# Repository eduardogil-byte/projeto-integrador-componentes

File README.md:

# 🔍 Sistema de Inspeção Automatizada de PCBs

Sistema de visão computacional desenvolvido para auxiliar na **inspeção de lotes de placas de circuito impresso (PCBs)**.

O projeto surgiu a partir de uma **demanda real apresentada por uma instituição da área de pesquisa**, que precisava verificar placas eletrônicas de forma mais rápida e padronizada.

A aplicação utiliza os arquivos de fabricação da placa juntamente com fotografias da PCB montada para localizar e verificar seus componentes.

> 🚧 Projeto em fase final de desenvolvimento e validação.

---

## 📌 Sobre o projeto

A inspeção manual de placas eletrônicas pode exigir a conferência de dezenas ou centenas de componentes em cada PCB.

Quando esse processo precisa ser repetido em vários exemplares de um mesmo lote, a inspeção pode se tornar demorada e sujeita a inconsistências.

O objetivo deste projeto é utilizar **visão computacional** para auxiliar esse processo.

O sistema recebe informações da fabricação da placa e uma imagem da PCB montada, realiza o alinhamento entre elas e verifica individualmente os componentes esperados.

---

## 🎯 Objetivo

O sistema foi desenvolvido para auxiliar na identificação de problemas como:

* componentes ausentes;
* componentes cuja presença não pôde ser confirmada;
* diferenças entre a placa montada e os dados esperados;
* problemas de alinhamento ou qualidade da imagem que impeçam uma inspeção confiável.

O objetivo não é apenas indicar um resultado, mas também facilitar a análise do operador durante a inspeção de um lote.

---

## 🧠 Como funciona

De forma simplificada, o processo de inspeção segue este fluxo:

```text
Arquivos da placa
        +
Foto da PCB montada
        ↓
Identificação da placa
        ↓
Alinhamento por homografia
        ↓
Localização dos componentes
        ↓
Recorte das regiões de interesse
        ↓
Análise por visão computacional
        ↓
Classificação dos componentes
        ↓
Resultado da inspeção
```

---

## 📐 Alinhamento da placa

Uma das etapas mais importantes do sistema é alinhar corretamente a fotografia da placa real com a referência utilizada pelo software.

Para isso, o sistema utiliza **homografia**, permitindo relacionar as coordenadas dos componentes presentes nos arquivos de fabricação com suas posições na fotografia.

Esse processo permite que o software saiba onde cada componente deveria estar mesmo quando a imagem apresenta diferenças de:

* posição;
* escala;
* perspectiva;
* rotação.

Caso o alinhamento não possua qualidade suficiente, o sistema evita realizar classificações que poderiam produzir resultados incorretos.

---

## 🔎 Inspeção dos componentes

Após o alinhamento, cada região correspondente a um componente é localizada e recortada.

Essas imagens são analisadas individualmente para determinar se o componente está presente.

Os resultados podem ser classificados em estados como:

```text
✅ Presente
⚠️ Incerto
❌ Ausente
```

Resultados considerados incertos podem ser posteriormente avaliados pelo operador.

---

## 🧩 Dados da placa

O sistema utiliza informações provenientes dos arquivos de fabricação da PCB para saber quais componentes devem estar presentes e onde eles estão posicionados.

Entre as informações utilizadas estão dados como:

* referência do componente;
* coordenadas X e Y;
* encapsulamento;
* posição esperada na placa.

Esses dados são combinados com a análise da imagem da placa montada.

---

## 🛠️ Tecnologias utilizadas

O projeto utiliza diferentes ferramentas de visão computacional e desenvolvimento de software, incluindo:

* **Python**
* **OpenCV**
* **YOLO**
* **MobileNet**
* **Processamento de imagens**
* **Homografia**
* **Gerber**
* **Dados de posicionamento de componentes**
* **HTML**
* **CSS**
* **JavaScript**

---

## 🤖 Visão computacional

O sistema combina diferentes técnicas para realizar a inspeção.

### OpenCV

Utilizado em etapas de processamento e análise das imagens, incluindo transformações, recortes e alinhamento.

### Homografia

Responsável por relacionar a imagem capturada da placa com o sistema de coordenadas utilizado pelos arquivos da PCB.

### MobileNet

Utilizada na análise das regiões dos componentes para auxiliar na classificação da presença dos componentes.

### YOLO

Utilizado como parte do processo de detecção e alinhamento visual da placa.

---

## 🖥️ Interface

O software também possui uma interface para facilitar o processo de inspeção.

A interface permite acompanhar os resultados obtidos pelo sistema e identificar rapidamente componentes que precisam de atenção.

A proposta é manter o operador dentro do processo, permitindo que casos inconclusivos possam ser avaliados manualmente.

---

## 🏭 Aplicação prática

O projeto foi desenvolvido pensando em um cenário real de inspeção de **lotes de placas eletrônicas**.

Em vez de verificar manualmente cada posição da placa, o operador pode utilizar o software como apoio para identificar rapidamente regiões que apresentam possíveis problemas.

Isso permite concentrar a inspeção humana nos componentes que realmente precisam de análise.

---

## 📊 Resultados da inspeção

Durante uma inspeção, o sistema analisa individualmente os componentes esperados na placa e gera um resultado para cada posição.

Esses resultados podem então ser utilizados para visualizar:

* componentes confirmados;
* componentes que precisam de revisão;
* possíveis ausências;
* problemas relacionados à captura da imagem ou alinhamento.

---

## 🚧 Status do projeto

O software encontra-se em **fase final de desenvolvimento e validação**.

Esta versão representa a primeira implementação do sistema de inspeção e serviu como base para novas melhorias e experimentos realizados durante a evolução do projeto.

---

## 🎓 Contexto

O projeto foi desenvolvido como **Projeto Integrador**, partindo de uma necessidade apresentada por uma instituição atuante na área de pesquisa.

A proposta permitiu aplicar conhecimentos de desenvolvimento de software e visão computacional em um problema real relacionado à inspeção de placas eletrônicas.

---

## 🧠 Conceitos aplicados

Durante o desenvolvimento foram aplicados conceitos como:

* visão computacional;
* processamento de imagens;
* homografia;
* detecção de objetos;
* classificação de imagens;
* transformação de coordenadas;
* processamento de arquivos de fabricação de PCBs;
* integração entre frontend e processamento de imagens;
* validação de resultados;
* desenvolvimento orientado a uma necessidade real.

---

## 👨‍💻 Autores

**Eduardo Machado Gil**
GitHub: [@eduardogil-byte](https://github.com/eduardogil-byte)

**Luiz Gustavo da Silva Campos**
GitHub: [@luizcamposss](https://github.com/luizcamposss)

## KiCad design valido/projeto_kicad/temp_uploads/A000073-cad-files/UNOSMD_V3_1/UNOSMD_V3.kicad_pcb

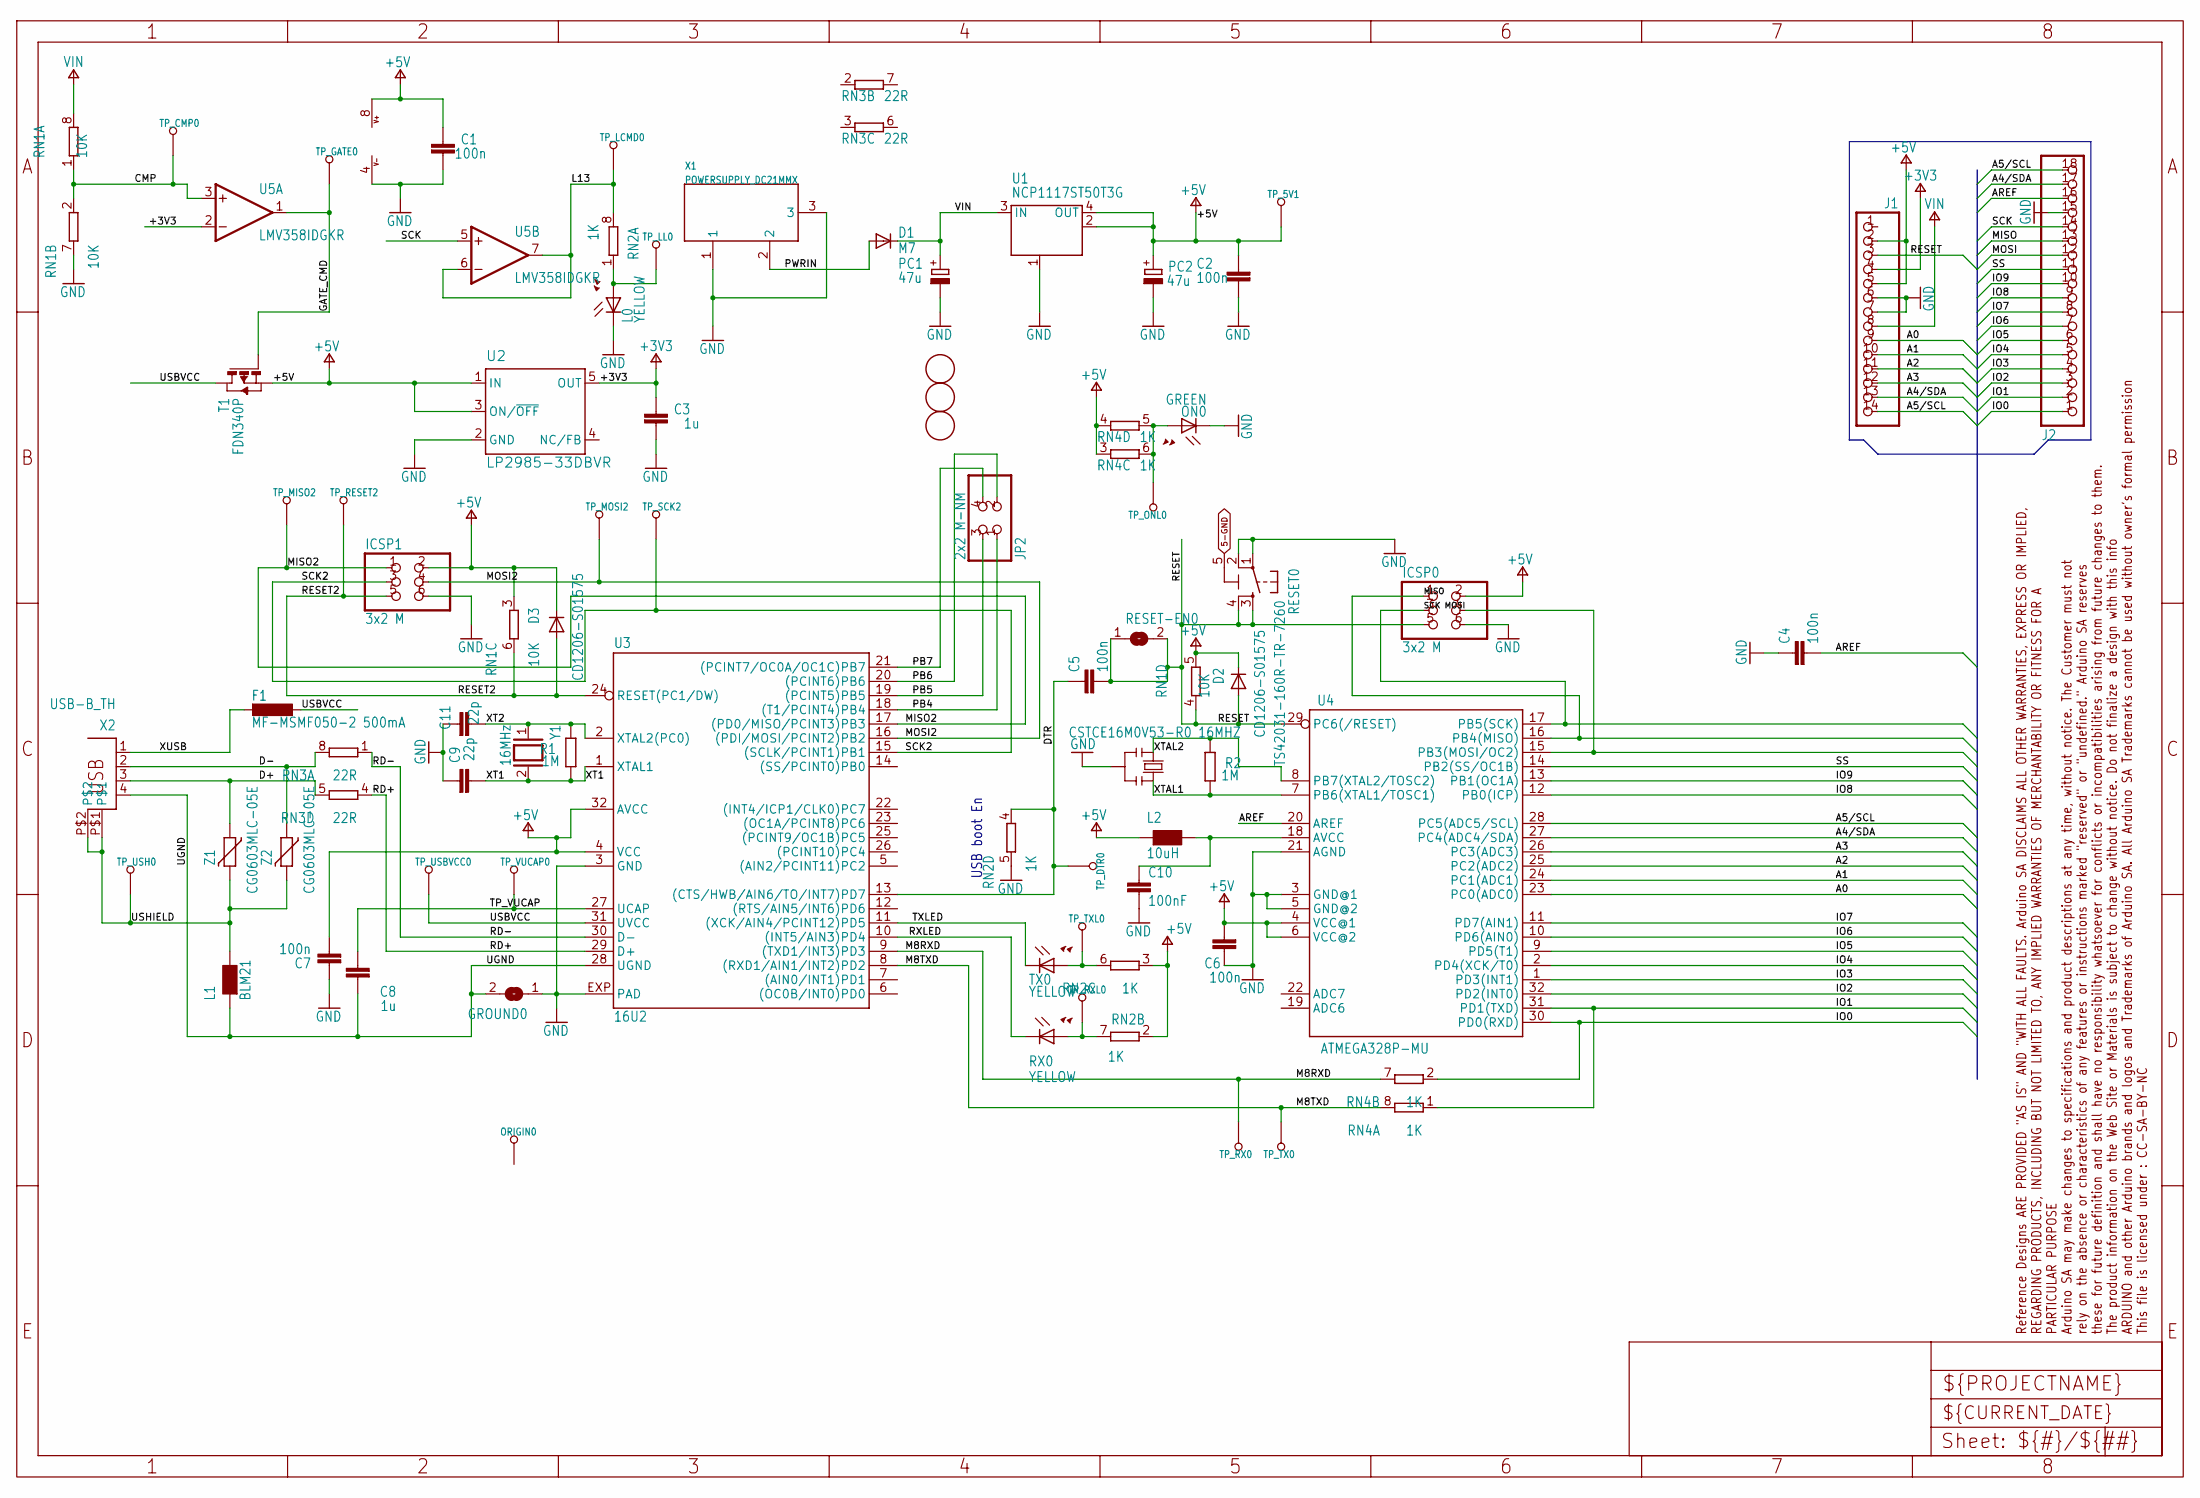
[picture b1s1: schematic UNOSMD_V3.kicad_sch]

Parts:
C1, C2, C4, C5, C6, C7: 100n; C0603-ROUND
C3, C8: 1u; C0603-ROUND
C9, C11: 22p; C0603-ROUND
C10: 100nF; C0603-ROUND
D1: M7; SMB
D2, D3: CD1206-S01575; MINIMELF
F1: MF-MSMF050-2 500mA; L1812
FD1, FD2, FD3: DNP; FD-1-1.5
FRAME1: DNP; FRAME
GROUND0: SJ
ICSP0, ICSP1: 3x2 M; 2X03
J1: -; 1X14-CUSTOM
J2: -; 1X18-CUSTOM
JP2: 2x2 M-NM; 2X02
L0: YELLOW; CHIP-LED0805
L1: BLM21; 0805
L2: 10uH; 0805
ON0: GREEN; CHIP-LED0805
ORIGIN0: TP_SP; TP-SP
PC1, PC2: 47u; PANASONIC_D
R1, R2: 1M; R0603-ROUND
RESET0: TS42031-160R-TR-7260; TS42
RESET-EN0: SJ
RN1: 10K; CAY16
RN2, RN4: 1K; CAY16
RN3: 22R; CAY16
RX0: YELLOW; CHIP-LED0805
T1: FDN340P; SOT-23
TP_5V1: TP_SP; TP-SP
TP_CMP0: TP_SP; TP-SP
TP_DTR0: TP_SP; TP-SP
TP_GATE0: TP_SP; TP-SP
TP_LCMD0: TP_SP; TP-SP
TP_LL0: TP_SP; TP-SP
TP_MISO2: TP_SP; TP-SP
TP_MOSI2: TP_SP; TP-SP
TP_ONL0: TP_SP; TP-SP
TP_RESET2: TP_SP; TP-SP
TP_RX0: TP_SP; TP-SP
TP_RXL0: TP_SP; TP-SP
TP_SCK2: TP_SP; TP-SP
TP_TX0: TP_SP; TP-SP
TP_TXL0: TP_SP; TP-SP
TP_USBVCC0: TP_SP; TP-SP
TP_USH0: TP_SP; TP-SP
TP_VUCAP0: TP_SP; TP-SP
TX0: YELLOW; CHIP-LED0805
U1: NCP1117ST50T3G; SOT223
U2: LP2985-33DBVR; SOT23-DBV
U3: 16U2; ATMEL_QFN32
U4: ATMEGA328P-MU; MLF32
U5: LMV358IDGKR; MSOP08
X1: POWERSUPPLY_DC21MMX; POWERSUPPLY_DC-21MM
X2: USB-B_TH; PN61729
Y1: 16MHz; QS
Y2: CSTCE16M0V53-R0 16MHZ; RESONATOR
Z1, Z2: CG0603MLC-05E; CT_CN0603

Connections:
5-GND: RESET0.5 (5-GND)
+3V3: C3.2, J1.4, U2.5 (OUT), U5.2 (-IN)
+5V: C1.2, C2.2, C6.2, C7.1, D2.C, D3.C, ICSP0.2, ICSP1.2, J1.2, J1.5, L2.1, PC2.+, RN1.3 (1), RN1.5 (2), RN2.2 (1), RN2.3 (1), RN4.3 (1), RN4.4 (1), T1.2 (S), TP_5V1.X, U1.2 (OUT@1), U1.4 (OUT), U2.1 (IN), U2.3 (ON/~OFF), U3.4 (VCC), U3.32 (AVCC), U4.4 (VCC@1), U4.6 (VCC@2), U5.8 (V+)
A0: J1.9, U4.23 (PC0(ADC0))
A1: J1.10, U4.24 (PC1(ADC1))
A2: J1.11, U4.25 (PC2(ADC2))
A3: J1.12, U4.26 (PC3(ADC3))
A4/SDA: J1.13, J2.17, U4.27 (PC4(ADC4/SDA))
A5/SCL: J1.14, J2.18, U4.28 (PC5(ADC5/SCL))
AREF: C4.2, J2.16, U4.20 (AREF)
CMP: RN1.1, RN1.2 (1), TP_CMP0.X, U5.3 (+IN)
D+: RN3.5 (2), X2.3, Z1.1
D-: RN3.8 (2), X2.2, Z2.1
DTR: C5.1, RN2.4 (1), TP_DTR0.X, U3.13 ((CTS/HWB/AIN6/TO/INT7)PD7)
GATE_CMD: T1.3 (G), TP_GATE0.X, U5.1 (OUT)
GND: C1.1, C2.1, C3.1, C4.1, C6.1, C7.2, C9.2, C10.2, C11.2, GROUND0.1, ICSP0.6, ICSP1.6, J1.6, J1.7, J2.15, L0.C, ON0.C, PC1.-, PC2.-, RESET0.1, RESET0.2, RN1.7 (2), RN2.5 (2), U1.1 (GND/ADJ), U2.2 (GND), U3.3 (GND), U3.EXP (PAD), U4.3 (GND@1), U4.5 (GND@2), U4.21 (AGND), U5.4 (V-), X1.1, X1.3, Y2.2
IO0: J2.1, RN4.2 (1), U4.30 (PD0(RXD))
IO1: J2.2, RN4.1, U4.31 (PD1(TXD))
IO2: J2.3, U4.32 (PD2(INT0))
IO3: J2.4, U4.1 (PD3(INT1))
IO4: J2.5, U4.2 (PD4(XCK/T0))
IO5: J2.6, U4.9 (PD5(T1))
IO6: J2.7, U4.10 (PD6(AIN0))
IO7: J2.8, U4.11 (PD7(AIN1))
IO8: J2.9, U4.12 (PB0(ICP))
IO9: J2.10, U4.13 (PB1(OC1A))
L13: RN2.8 (2), TP_LCMD0.X, U5.6 (-IN), U5.7 (OUT)
M8RXD: RN4.7 (2), TP_RX0.X, U3.9 ((TXD1/INT3)PD3)
M8TXD: RN4.8 (2), TP_TX0.X, U3.8 ((RXD1/AIN1/INT2)PD2)
MISO: ICSP0.1, J2.13, U4.16 (PB4(MISO))
MISO2: ICSP1.1, TP_MISO2.X, U3.17 ((PD0/MISO/PCINT3)PB3)
MOSI: ICSP0.4, J2.12, U4.15 (PB3(MOSI/OC2))
MOSI2: ICSP1.4, TP_MOSI2.X, U3.16 ((PDI/MOSI/PCINT2)PB2)
unnamed: L0.A, RN2.1, TP_LL0.X
unnamed: ON0.A, RN4.5 (2), RN4.6 (2), TP_ONL0.X
unnamed: C10.1, L2.2, U4.18 (AVCC)
unnamed: RN2.7 (2), RX0.A, TP_RXL0.X
unnamed: RN2.6 (2), TP_TXL0.X, TX0.A
PB4: JP2.1, U3.18 ((T1/PCINT4)PB4)
PB5: JP2.3, U3.19 ((PCINT5)PB5)
PB6: JP2.2, U3.20 ((PCINT6)PB6)
PB7: JP2.4, U3.21 ((PCINT7/OC0A/OC1C)PB7)
PWRIN: D1.A, X1.2
RD+: RN3.4 (1), U3.29 (D+)
RD-: RN3.1, U3.30 (D-)
RESET: C5.2, D2.A, ICSP0.5, J1.3, RESET0.3, RESET0.4, RESET-EN0.1, RESET-EN0.2, RN1.4 (1), U4.29 (PC6(/RESET))
RESET2: D3.A, ICSP1.5, RN1.6 (2), TP_RESET2.X, U3.24 (RESET(PC1/DW))
RXLED: RX0.C, U3.10 ((INT5/AIN3)PD4)
SCK: ICSP0.3, J2.14, U4.17 (PB5(SCK)), U5.5 (+IN)
SCK2: ICSP1.3, TP_SCK2.X, U3.15 ((SCLK/PCINT1)PB1)
SS: J2.11, U4.14 (PB2(SS/OC1B))
TP_VUCAP: C8.1, TP_VUCAP0.X, U3.27 (UCAP)
TXLED: TX0.C, U3.11 ((XCK/AIN4/PCINT12)PD5)
UGND: C8.2, GROUND0.2, L1.1, U3.28 (UGND), X2.4
USBVCC: F1.1, T1.1 (D), TP_USBVCC0.X, U3.31 (UVCC)
USHIELD: L1.2, TP_USH0.X, X2.P$1, X2.P$2, Z1.2, Z2.2
VIN: D1.C, J1.8, PC1.+, RN1.8 (2), U1.3 (IN)
XT1: C9.1, R1.1, U3.1 (XTAL1), Y1.2
XT2: C11.1, R1.2, U3.2 (XTAL2(PC0)), Y1.1
XTAL1: R2.1, U4.7 (PB6(XTAL1/TOSC1)), Y2.3
XTAL2: R2.2, U4.8 (PB7(XTAL2/TOSC2)), Y2.1
XUSB: F1.2, X2.1

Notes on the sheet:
USB boot En

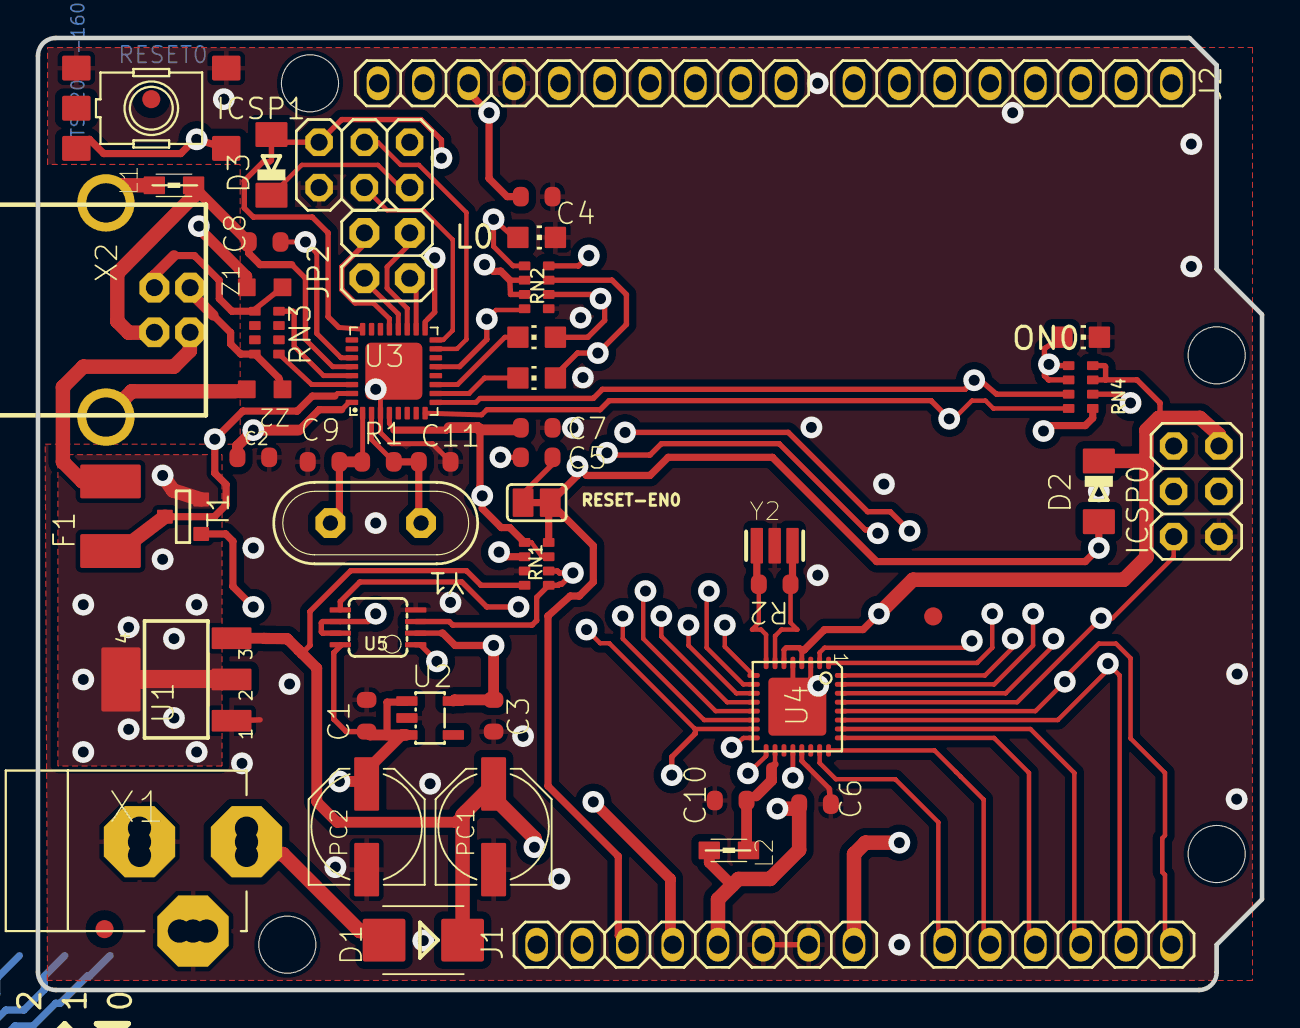
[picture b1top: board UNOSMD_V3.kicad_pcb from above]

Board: 2 copper layers, 68.6 x 53.3 mm, 76 parts (1 on the bottom side), 61 nets.

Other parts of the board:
UNK_HOLE_0: dummyfp0
UNK_HOLE_1: dummyfp1
UNK_HOLE_2: dummyfp2
UNK_HOLE_3: dummyfp3

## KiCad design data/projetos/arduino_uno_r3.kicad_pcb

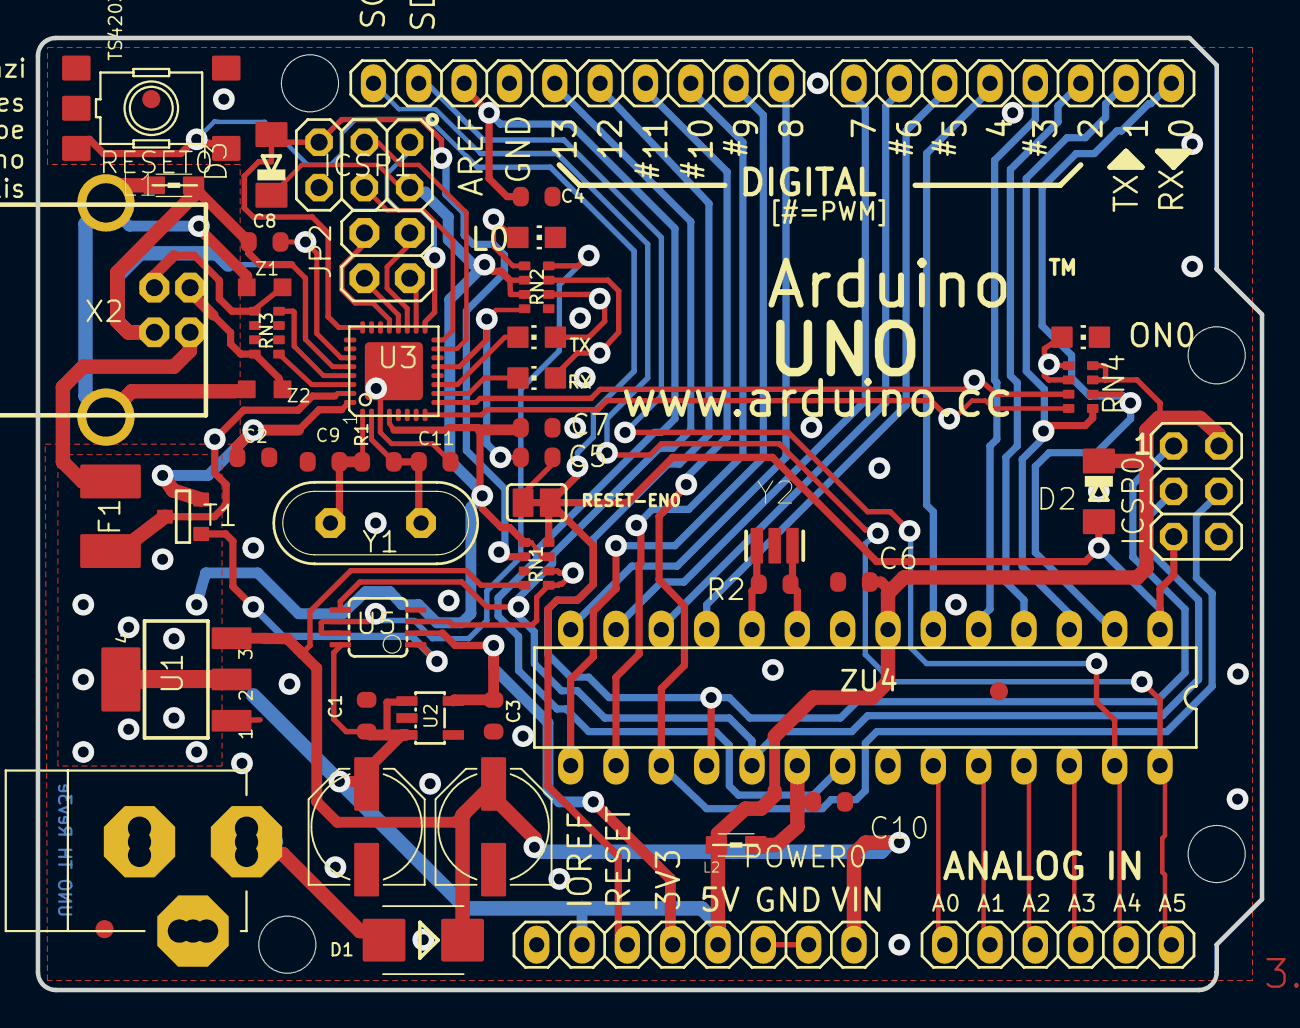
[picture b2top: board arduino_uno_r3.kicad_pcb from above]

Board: 2 copper layers, 68.6 x 53.3 mm, 120 parts (1 on the bottom side), 61 nets.

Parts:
AD0: 6x1F-H8.5; 1X06
C1, C2, C4, C5, C6, C7, C10: 100n; C0603-ROUND
C3, C8: 1u; C0603-ROUND
C9, C11: 22p; C0603-ROUND
D1: M7; SMB
D2, D3: CD1206-S01575; MINIMELF
F1: MF-MSMF050-2 500mA; L1812
FD1, FD2, FD3: FIDUCIALMOUNT; FIDUCIA-MOUNT
FRAME1: DNP; FRAME
GND_TP0, GND_TP1: TP_SP; TP-SP
GROUND0: SJ
ICSP0, ICSP1: 3x2 M; 2X03
IOH0: 10x1F-H8.5; 1X10
IOL0: 8x1F-H8.5; 1X08
JP2: 2x2 M - NM; 2X02
L0: YELLOW; CHIP-LED0805
L1: BLM21; 0805
L2: 10uH; 0805
ON0: GREEN; CHIP-LED0805
ORIGIN0: TP_SP; TP-SP
PC1, PC2: 47u; PANASONIC_D
POWER0: 8x1F-H8.5; 1X08
R1, R2: 1M; R0603-ROUND
RESET0: TS42031-160R-TR-7260; TS42
RESET-EN0: SJ
RN1: 10K; CAY16
RN2, RN4: 1K; CAY16
RN3: 22R; CAY16
RX0: YELLOW; CHIP-LED0805
T1: FDN340P; SOT-23
TP_0, TP_1, TP_2, TP_3, TP_3V3, TP_4, TP_5, TP_5V0, TP_5V1, TP_6, TP_7, TP_8, TP_9, TP_10, TP_11, TP_12, TP_13: TP_SP; TP-SP
TP_A0, TP_A1, TP_A2, TP_A3, TP_A4, TP_A5: TP_SP; TP-SP
TP_AREF0: TP_SP; TP-SP
TP_CMP0: TP_SP; TP-SP
TP_D+0: TP_SP; TP-SP
TP_D-0: TP_SP; TP-SP
TP_DTR0: TP_SP; TP-SP
TP_GATE0: TP_SP; TP-SP
TP_LCMD0: TP_SP; TP-SP
TP_LL0: TP_SP; TP-SP
TP_MISO2: TP_SP; TP-SP
TP_MOSI2: TP_SP; TP-SP
TP_ONL0: TP_SP; TP-SP
TP_PB4, TP_PB5, TP_PB6, TP_PB7: TP_SP; TP-SP
TP_PWRIN0: TP_SP; TP-SP
TP_RESET0, TP_RESET2: TP_SP; TP-SP
TP_RX0: TP_SP; TP-SP
TP_RXL0: TP_SP; TP-SP
TP_SCK2: TP_SP; TP-SP
TP_SCL0: TP_SP; TP-SP
TP_SDA0: TP_SP; TP-SP
TP_TX0: TP_SP; TP-SP
TP_TXL0: TP_SP; TP-SP
TP_UGND0: TP_SP; TP-SP
TP_USBVCC0: TP_SP; TP-SP
TP_USH0: TP_SP; TP-SP
TP_VIN0: TP_SP; TP-SP
TP_VUCAP0: TP_SP; TP-SP
TP_XT1, TP_XT2, TP_XT3, TP_XT4: TP_SP; TP-SP
TP_XUSB0: TP_SP; TP-SP
TX0: YELLOW; CHIP-LED0805
U1: NCP1117ST50T3G; SOT223
U2: LP2985-33DBVR; SOT23-DBV
U3: ATMEGA16U2-MU(R); MLF32
U5: LMV358IDGKR; MSOP08
UNK_HOLE_0: dummyfp0
UNK_HOLE_1: dummyfp1
UNK_HOLE_2: dummyfp2
UNK_HOLE_3: dummyfp3
X1: POWERSUPPLY_DC21MMX; POWERSUPPLY_DC-21MM
X2: USB-B_TH; PN61729
Y1: 16MHz; QS
Y2: CSTCE16M0V53-R0 16MHZ; RESONATOR
Z1, Z2: CG0603MLC-05E; CT_CN0603
ZU4: ATMEGA328P-PU; DIL28-3

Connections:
+3V3: C3.2, POWER0.4, TP_3V3.X, U2.5, U5.2
+5V: C1.2, C2.2, C6.2, C7.1, D2.C, D3.C, ICSP0.2, ICSP1.2, L2.1, PC2.+, POWER0.2, POWER0.5, RN1.3, RN1.5, RN2.2, RN2.3, RN4.3, RN4.4, T1.2, TP_5V0.X, TP_5V1.X, U1.2, U1.4, U2.1, U2.3, U3.4, U3.32, U5.8, ZU4.7
AD0: AD0.1, TP_A0.X, ZU4.23
AD1: AD0.2, TP_A1.X, ZU4.24
AD2: AD0.3, TP_A2.X, ZU4.25
AD3: AD0.4, TP_A3.X, ZU4.26
AD4/SDA: AD0.5, IOH0.9, TP_A4.X, TP_SDA0.X, ZU4.27
AD5/SCL: AD0.6, IOH0.10, TP_A5.X, TP_SCL0.X, ZU4.28
AREF: C4.2, IOH0.8, TP_AREF0.X, ZU4.21
AVCC: C10.2, L2.2, ZU4.20
CMP: RN1.1, RN1.2, TP_CMP0.X, U5.3
D+: RN3.5, TP_D+0.X, X2.3, Z1.1
D-: RN3.8, TP_D-0.X, X2.2, Z2.1
DTR: C5.1, RN2.4, TP_DTR0.X, U3.13
GATE_CMD: T1.3, TP_GATE0.X, U5.1
GND: C1.1, C2.1, C3.1, C4.1, C6.1, C7.2, C9.2, C10.1, C11.2, GND_TP0.X, GND_TP1.X, GROUND0.1, ICSP0.6, ICSP1.6, IOH0.7, L0.C, ON0.C, PC1.-, PC2.-, POWER0.6, POWER0.7, RESET0.1, RESET0.2, RN1.7, RN2.5, U1.1, U2.2, U3.3, U3.33, U5.4, X1.1, X1.3, Y2.2, ZU4.8, ZU4.22
IO0: IOL0.1, RN4.2, TP_0.X, ZU4.2
IO1: IOL0.2, RN4.1, TP_1.X, ZU4.3
IO2: IOL0.3, TP_2.X, ZU4.4
IO3: IOL0.4, TP_3.X, ZU4.5
IO4: IOL0.5, TP_4.X, ZU4.6
IO5: IOL0.6, TP_5.X, ZU4.11
IO6: IOL0.7, TP_6.X, ZU4.12
IO7: IOL0.8, TP_7.X, ZU4.13
IO8: IOH0.1, TP_8.X, ZU4.14
IO9: IOH0.2, TP_9.X, ZU4.15
L13: RN2.8, TP_LCMD0.X, U5.6, U5.7
M8RXD: RN4.7, TP_RX0.X, U3.9
M8TXD: RN4.8, TP_TX0.X, U3.8
MISO: ICSP0.1, IOH0.5, TP_12.X, ZU4.18
MISO2: ICSP1.1, TP_MISO2.X, U3.17
MOSI: ICSP0.4, IOH0.4, TP_11.X, ZU4.17
MOSI2: ICSP1.4, TP_MOSI2.X, U3.16
unnamed: L0.A, RN2.1, TP_LL0.X
unnamed: ON0.A, RN4.5, RN4.6, TP_ONL0.X
unnamed: RN2.7, RX0.A, TP_RXL0.X
unnamed: RN2.6, TP_TXL0.X, TX0.A
PB4: JP2.1, TP_PB4.X, U3.18
PB5: JP2.3, TP_PB5.X, U3.19
PB6: JP2.2, TP_PB6.X, U3.20
PB7: JP2.4, TP_PB7.X, U3.21
PWRIN: D1.A, TP_PWRIN0.X, X1.2
RD+: RN3.4, U3.29
RD-: RN3.1, U3.30
RESET: C5.2, D2.A, ICSP0.5, POWER0.3, RESET0.3, RESET0.4, RESET-EN0.1, RESET-EN0.2, RN1.4, TP_RESET0.X, ZU4.1
RESET2: D3.A, ICSP1.5, RN1.6, TP_RESET2.X, U3.24
RXLED: RX0.C, U3.10
SCK: ICSP0.3, IOH0.6, TP_13.X, U5.5, ZU4.19
SCK2: ICSP1.3, TP_SCK2.X, U3.15
SS: IOH0.3, TP_10.X, ZU4.16
TP_VUCAP: C8.1, TP_VUCAP0.X, U3.27
TXLED: TX0.C, U3.11
UGND: C8.2, GROUND0.2, L1.1, TP_UGND0.X, U3.28, X2.4
USBVCC: F1.1, T1.1, TP_USBVCC0.X, U3.31
USHIELD: L1.2, TP_USH0.X, X2.P$1, X2.P$2, Z1.2, Z2.2
VIN: D1.C, PC1.+, POWER0.8, RN1.8, TP_VIN0.X, U1.3
XT1: C9.1, R1.1, TP_XT3.X, U3.1, Y1.2
XT2: C11.1, R1.2, TP_XT4.X, U3.2, Y1.1
XTAL1: R2.1, TP_XT1.X, Y2.3, ZU4.9
XTAL2: R2.2, TP_XT2.X, Y2.1, ZU4.10
XUSB: F1.2, TP_XUSB0.X, X2.1

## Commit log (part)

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2026-04-02 criacao analyze
2026-04-02 testando analyze
2026-04-05 teste align auto
2026-04-05 align auto test
2026-04-08 comeco kicad
2026-04-09 teste
2026-04-22 create extrator_pcbnew
2026-04-22 fix pcbnew
2026-04-22 fix all
2026-04-22 refatoracao
2026-04-23 fix main
2026-04-24 fix points
2026-04-24 add .gitignore
2026-04-26 feat bom_footprint
2026-04-26 feat fastapi
2026-04-26 fix html
2026-04-26 melhoria index
2026-04-27 implementacao extrator
2026-04-27 fix extrator
2026-04-28 teste nao funcional

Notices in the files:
valido/projeto_kicad/temp_uploads/A000073-cad-files/UNOSMD_V3_1/UNOSMD_V3.kicad_sch:
This file is licensed under : CC-SA-BY-NC
